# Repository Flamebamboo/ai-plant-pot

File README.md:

# SmartPlanter aka PixPlanter

This project is an emotive smart planter that plays an animation through its OLED screen depending on the conditions from the soil moisture, temperature & humidity sensors. It's also designed for portability with a 2000 MAH lipo battery and easy battery charging with USB type C from the ESP32 C6 from xiao. With this microcontroller it supports HomeKit and battery charging built it which i'm really excited about. The CAD design of this planter contains 2 seprate compartments. The inner pot and the outer pot. The inner pot has a snap fit design and drainage holes for water to safely exit throughout the pot. I will add an safety precautious by adding waterproof silicone for the 3d printed parts just in case if there will be leaks that can cause danger to the electronics on the housing of the outer case.

The reason I built this project is because I want my baby Monstera plant to be healthy on my desk! and it would also be a great addition as decoration too!

### Additionaly I've made some short vlogs on my Youtube channel and my brand new Instagram account
https://youtube.com/shorts/UrM3IPHNWJw?si=KoA7QMxdPpVGsMg
I'm definitely planning to create long form yt vid for this project when it's fully completed :)

> **⚠️ Warning:** I will be writing the firmware when the MCU arrive and I'm planning to create a Swift or React Native app for this smart planter to control and customise the planter features! :)) .
> 

## Bill of Materials (BOM)

| Component                                                | Link                                                                                                                                                                                                                                                                                                                                                                                                                                                                                                                                                                                                                                                                       | Price (USD) |
| -------------------------------------------------------- | -------------------------------------------------------------------------------------------------------------------------------------------------------------------------------------------------------------------------------------------------------------------------------------------------------------------------------------------------------------------------------------------------------------------------------------------------------------------------------------------------------------------------------------------------------------------------------------------------------------------------------------------------------------------------- | ----------- |
| XIAO ESP32 C6                                            | [AliExpress](https://www.aliexpress.com/item/3256807155424151.html?spm=a2g0o.productlist.main.7.5dfe44c7DGi66V&algo_pvid=54d3fcd6-866c-4398-af89-09dad632af99&algo_exp_id=54d3fcd6-866c-4398-af89-09dad632af99-5&pdp_ext_f=%7B%22order%22%3A%221027%22%2C%22eval%22%3A%221%22%7D&pdp_npi=4%40dis%21USD%2134.70%2114.23%21%21%21246.96%21101.25%21%40212a70c117535391509211632e52bf%2112000040340289942%21sea%21US%216176438218%21X&curPageLogUid=RA8caGmI48mw&utparam-url=scene%3Asearch%7Cquery_from%3A)                                                                                                                                                                  | $14.23      |
| 1.5 inch OLED display                                    | [Waveshare](https://www.waveshare.com/product/displays/oled/oled-3/1.5inch-rgb-oled-module.html)                                                                                                                                                                                                                                                                                                                                                                                                                                                                                                                                                                           | $16.59      |
| LIPO Battery 3.7V 2000mAH                                | [AliExpress](https://www.aliexpress.com/item/3256808031709894.html)                                                                                                                                                                                                                                                                                                                                                                                                                                                                                                                                                                                                        | $3.86       |
| DHT22 Temperature and Humidity Sensor                    | [AliExpress](https://www.aliexpress.com/item/2251832573586959.html?spm=a2g0o.productlist.main.2.15a520a4ch0HcL&algo_pvid=c44ac3dd-26cf-49a8-874e-61999ace946d&algo_exp_id=c44ac3dd-26cf-49a8-874e-61999ace946d-1&pdp_ext_f=%7B%22order%22%3A%221835%22%2C%22eval%22%3A%221%22%7D&pdp_npi=4%40dis%21USD%211.89%211.89%21%21%211.89%211.89%21%402102f0cc17535388375158486e6113%2162102476019%21sea%21US%216176438218%21X&curPageLogUid=eNimnjqnOY2I&utparam-url=scene%3Asearch%7Cquery_from%3A)                                                                                                                                                                              | $1.89       |
| Soil Sensor                                              | [DigiKey](https://www.digikey.my/en/products/detail/adafruit-industries-llc/4026/9745252)                                                                                                                                                                                                                                                                                                                                                                                                                                                                                                                                                                                  | $7.50       |
| M2 × 8mm Screws                                          | [AliExpress](https://www.aliexpress.com/item/2255800888609493.html?spm=a2g0o.productlist.main.3.51bdTDteTDteJS&algo_pvid=77c5efe2-1216-4a27-8056-b27e5afe6d93&algo_exp_id=77c5efe2-1216-4a27-8056-b27e5afe6d93-2&pdp_ext_f=%7B%22order%22%3A%223146%22%2C%22eval%22%3A%221%22%7D&pdp_npi=4%40dis%21USD%211.25%211.25%21%21%211.25%211.25%21%40212e508f17535909677188109ee111%2110000014184740413%21sea%21US%216176438218%21X&curPageLogUid=YiHkOTW8RFV0&utparam-url=scene%3Asearch%7Cquery_from%3A)                                                                                                                                                                        | $1.59       |
| M2.6 × 4mm Screws                                        | [AliExpress](https://www.aliexpress.com/item/2255800795894953.html?gps-id=pcStoreLeaderboard&scm=1007.22922.271278.0&scm_id=1007.22922.271278.0&scm-url=1007.22922.271278.0&pvid=9d1f35b8-b4ad-40c0-801f-28061212913c&_t=gps-id:pcStoreLeaderboard,scm-url:1007.22922.271278.0,pvid:9d1f35b8-b4ad-40c0-801f-28061212913c,tpp_buckets:668%232846%238115%232000&pdp_ext_f=%7B%22order%22%3A%222844%22%2C%22eval%22%3A%221%22%2C%22sceneId%22%3A%2212922%22%7D&pdp_npi=4%40dis%21USD%211.15%211.15%21%21%211.15%211.15%21%40214100f417536751956683208eb980%2110000013191635027%21rec%21US%216176438218%21X&spm=a2g0o.store_pc_home.smartLeaderboard_1182734993.4000982209705) | $1.29       |
| 2.54mm Pin Header Vertical (Soil moisture 2 pin)         | [AliExpress](https://www.aliexpress.us/item/2255801012106911.html?spm=a2g0o.productlist.main.1.1212ZwX3ZwX3yM&algo_pvid=95ee878d-e9d7-47cd-88db-d6d36a7bd0f9&algo_exp_id=95ee878d-e9d7-47cd-88db-d6d36a7bd0f9-10&pdp_ext_f=%7B%22order%22%3A%223740%22%2C%22eval%22%3A%221%22%7D&pdp_npi=4%40dis%21USD%211.28%211.28%21%21%211.28%211.28%21%40212a70c017538012890922455ec68c%2110000015275671643%21sea%21US%216176438218%21X&curPageLogUid=CJbmy5mJzpHa&utparam-url=scene%3Asearch%7Cquery_from%3A)                                                                                                                                                                        | $1.28       |
| 2.54mm Pin Header Vertical (OLED 7 pin)                  | [AliExpress](https://www.aliexpress.us/item/2255801012106911.html?spm=a2g0o.productlist.main.1.1212ZwX3ZwX3yM&algo_pvid=95ee878d-e9d7-47cd-88db-d6d36a7bd0f9&algo_exp_id=95ee878d-e9d7-47cd-88db-d6d36a7bd0f9-10&pdp_ext_f=%7B%22order%22%3A%223740%22%2C%22eval%22%3A%221%22%7D&pdp_npi=4%40dis%21USD%211.28%211.28%21%21%211.28%211.28%21%40212a70c017538012890922455ec68c%2110000015275671643%21sea%21US%216176438218%21X&curPageLogUid=CJbmy5mJzpHa&utparam-url=scene%3Asearch%7Cquery_from%3A)                                                                                                                                                                        | $1.46       |
| JST PH 2.0mm Male Female Plug Jack Connector Cable 20 cm | [AliExpress](https://www.aliexpress.us/item/3256803204628036.html?spm=a2g0o.productlist.main.2.579220d8qlf0I6&algo_pvid=3e7ca395-6d77-45fc-a44f-9e64c19d44b8&algo_exp_id=3e7ca395-6d77-45fc-a44f-9e64c19d44b8-15&pdp_ext_f=%7B%22order%22%3A%224234%22%2C%22eval%22%3A%221%22%7D&pdp_npi=4%40dis%21USD%211.68%211.68%21%21%211.68%211.68%21%402101062a17538014489517862e18b6%2112000025564240283%21sea%21US%216176438218%21X&curPageLogUid=FyO7RojxqDox&utparam-url=scene%3Asearch%7Cquery_from%3A)                                                                                                                                                                        | $1.74       |
| **Total**                                                |                                                                                                                                                                                                                                                                                                                                                                                                                                                                                                                                                                                                                                                                            | **$51.43**  |

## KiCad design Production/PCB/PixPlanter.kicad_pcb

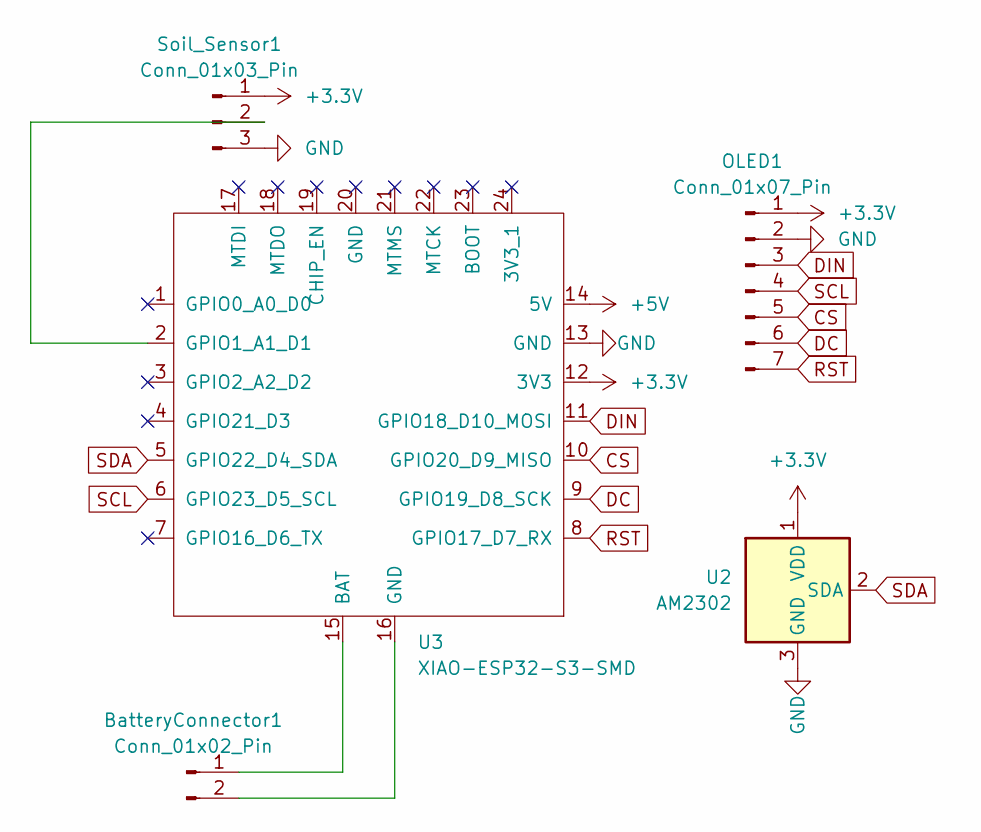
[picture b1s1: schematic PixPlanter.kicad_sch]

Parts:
BatteryConnector1: Conn_01x02_Pin; JST_PH_S2B-PH-K_1x02_P2.00mm_Horizontal
OLED1: Conn_01x07_Pin; PinHeader_1x07_P2.54mm_Vertical
Soil_Sensor1: Conn_01x03_Pin; PinHeader_1x03_P2.54mm_Vertical
U2: AM2302; ASAIR_AM2302_P2.54mm_Vertical
U3: XIAO-ESP32-S3-SMD; XIAO-ESP32C6-SMD

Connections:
+3.3V: OLED1.1, Soil_Sensor1.1, U2.1 (VDD), U3.12 (3V3)
+5V: U3.14 (5V)
CS: OLED1.5, U3.10 (GPIO20_D9_MISO)
DC: OLED1.6, U3.9 (GPIO19_D8_SCK)
DIN: OLED1.3, U3.11 (GPIO18_D10_MOSI)
GND: OLED1.2, Soil_Sensor1.3, U2.3 (GND), U2.4 (GND), U3.13 (GND)
unnamed: BatteryConnector1.1, U3.15 (BAT)
unnamed: BatteryConnector1.2, U3.16 (GND)
unnamed: Soil_Sensor1.2, U3.2 (GPIO1_A1_D1)
RST: OLED1.7, U3.8 (GPIO17_D7_RX)
SCL: OLED1.4, U3.6 (GPIO23_D5_SCL)
SDA: U2.2 (SDA), U3.5 (GPIO22_D4_SDA)

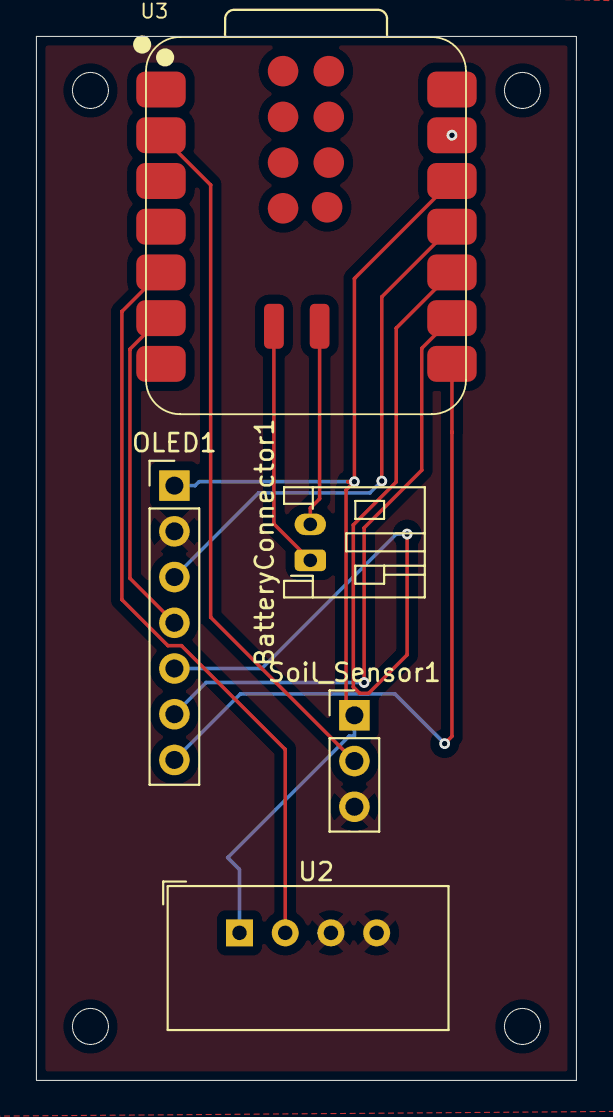
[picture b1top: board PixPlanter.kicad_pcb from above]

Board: 2 copper layers, 30.0 x 58.0 mm, 5 parts (0 on the bottom side), 11 nets.

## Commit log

2025-06-20 journal template
2025-06-20 added readme
2025-06-20 day 1
2025-06-20 added images for day 1.
2025-06-21 2 hours in 21st June
2025-06-21 1h30 mins in 21st June
2025-06-22 added BOM into readme
2025-06-22 add links
2025-06-22 2 hours into june 22th
2025-06-22 added image
2025-06-24 day 4!
2025-06-29 June 28 (late journal and commit)
2025-06-29 June 27th edited vlog
2025-07-02 July 1st
2025-07-03 July 2
2025-07-23 Added 23rd July
2025-07-23 base enclosure image
2025-07-26 removed light sensors
2025-07-26 Reduce sensor cost + update links
2025-07-27 July 27th
2025-07-28 BOM table
2025-07-28 Morning - Afternoon work
2025-07-28 Snap fit
2025-07-28 added final polishes
2025-07-28 Imported CAD files in production folder
2025-07-28 refine my journal and added gerbes for PCB
2025-07-29 added BOM and readme of short description of this project
2025-07-29 update BOM with AI
2025-07-29 final update?
2025-07-29 added Assembled step CAD
2025-08-02 Source file -rereview
    mistake on my end :(
